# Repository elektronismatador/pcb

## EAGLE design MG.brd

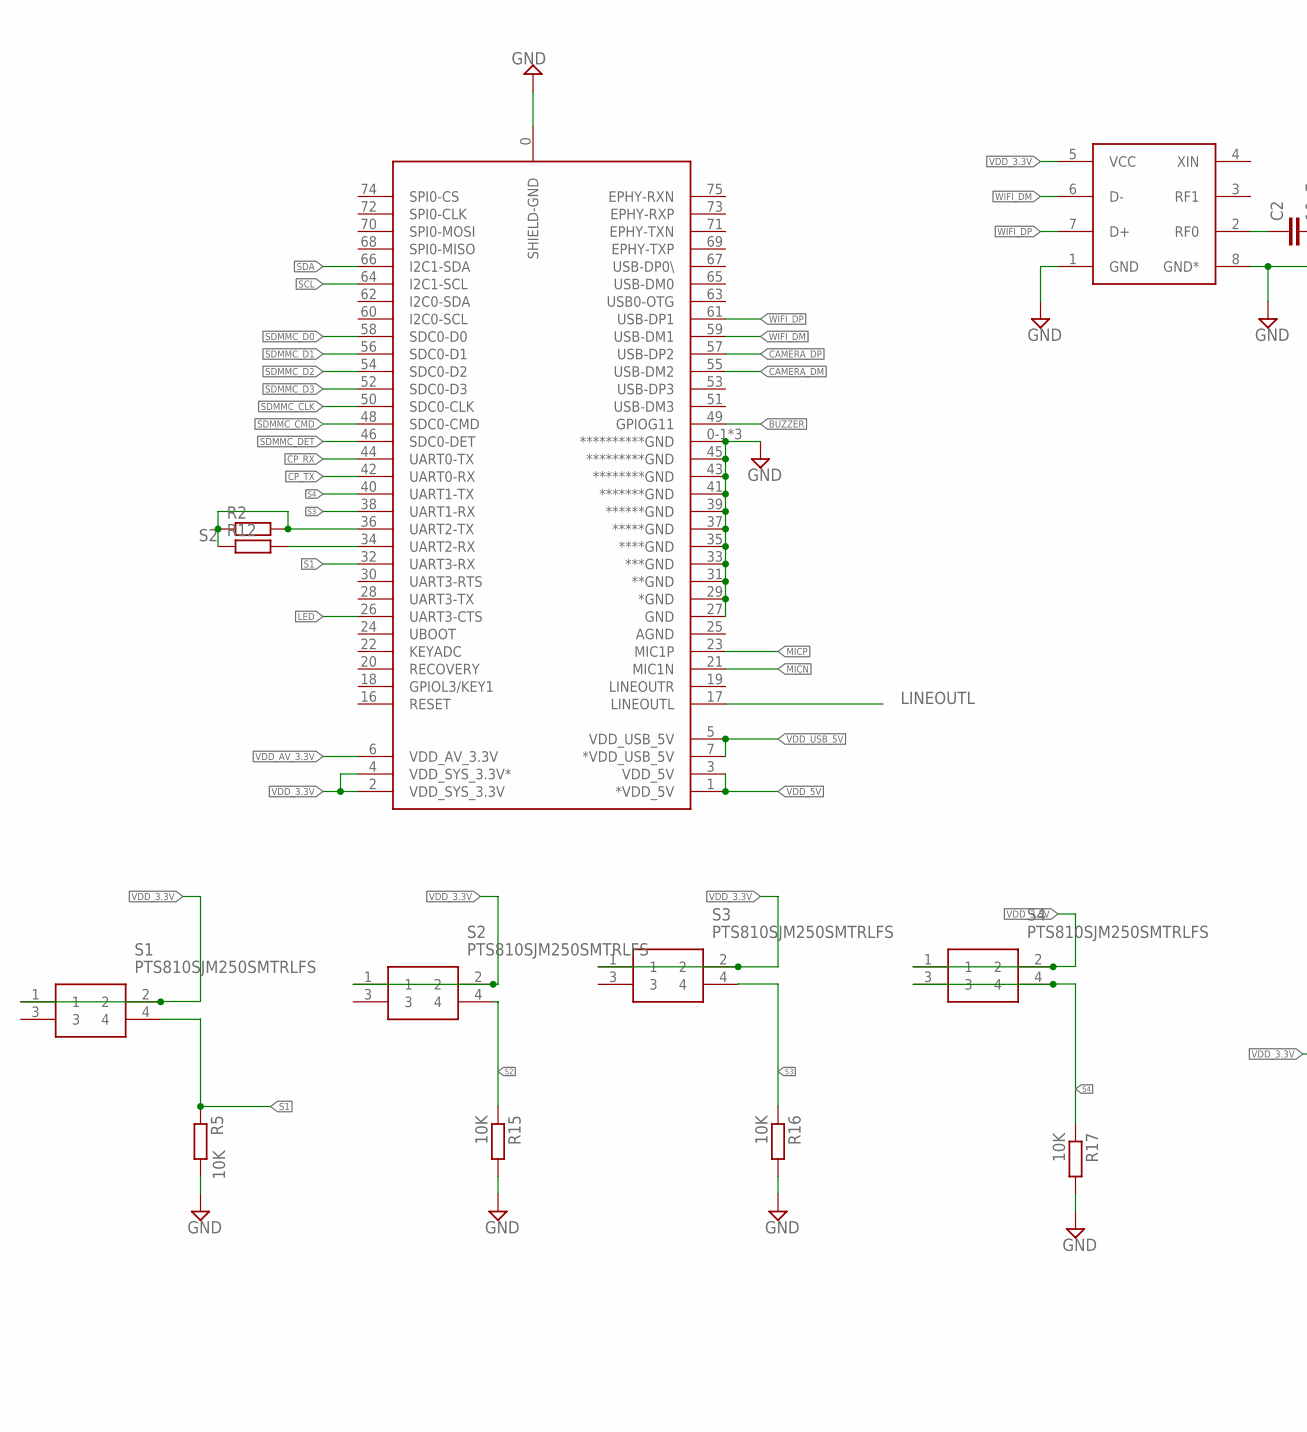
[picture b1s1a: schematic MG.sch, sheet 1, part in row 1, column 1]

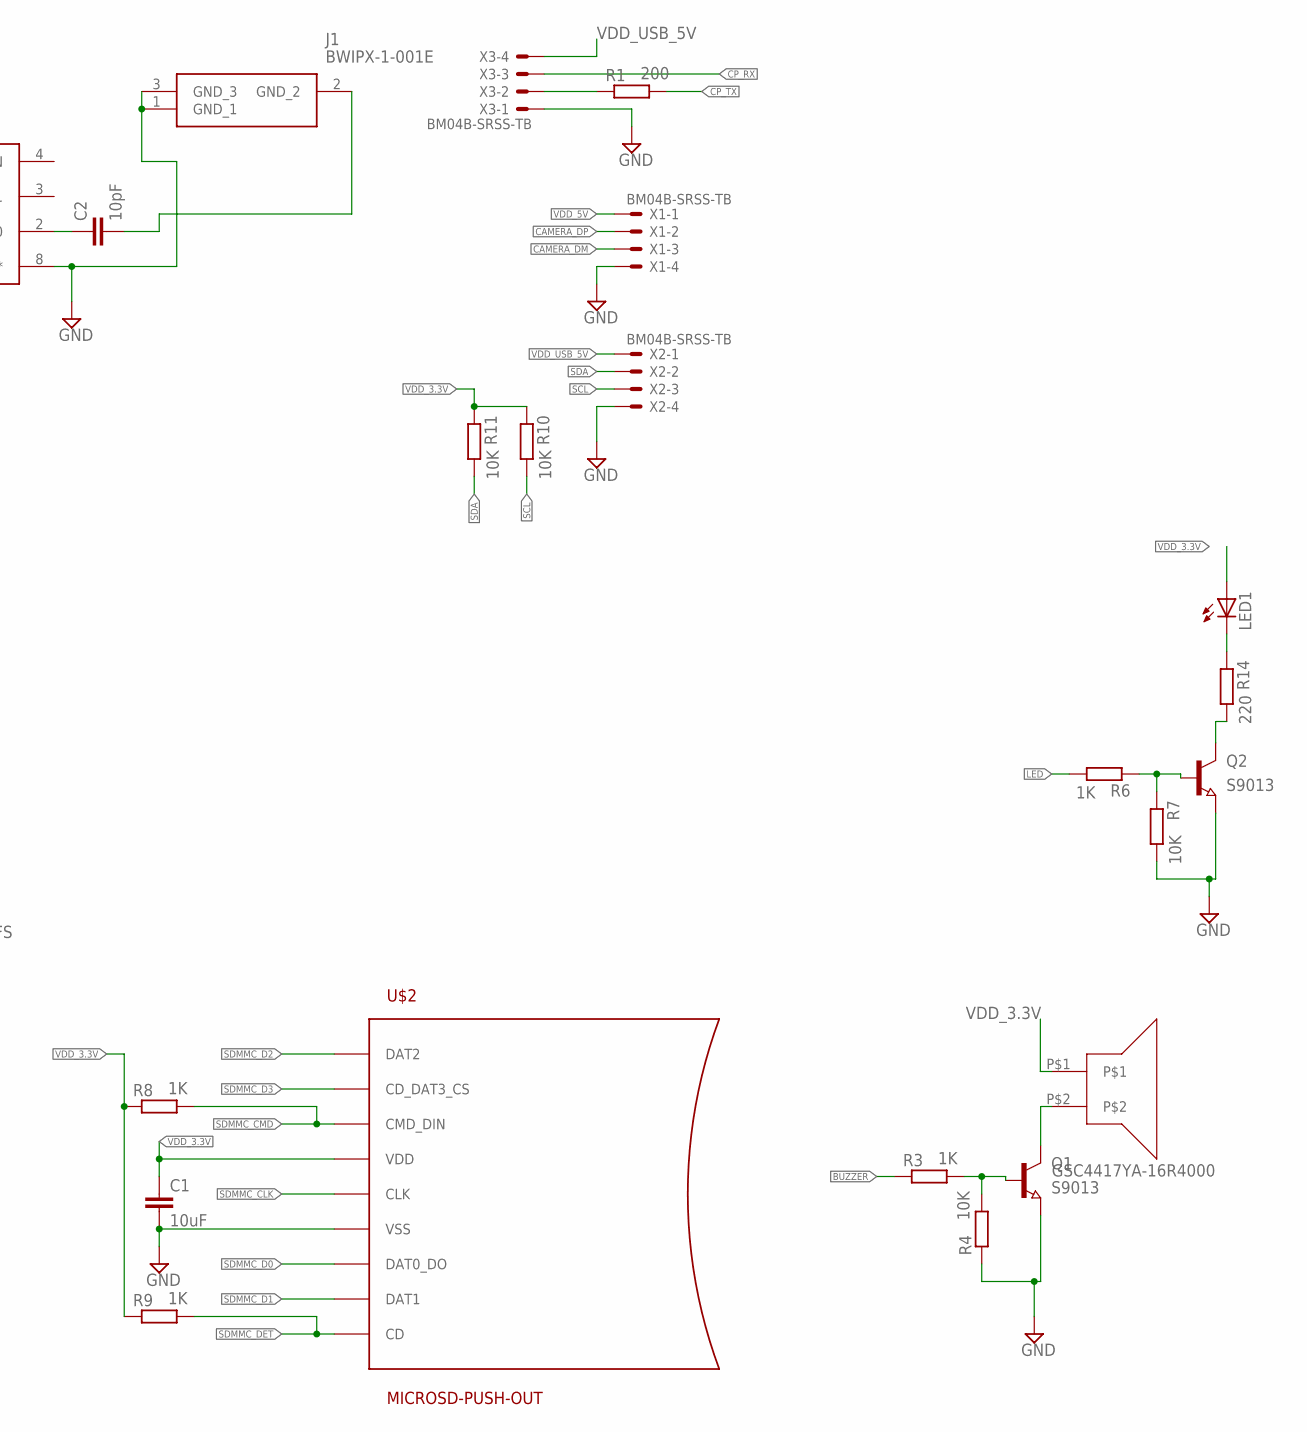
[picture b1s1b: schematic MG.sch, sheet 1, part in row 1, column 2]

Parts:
C1: 10uF; C0603
C2: 10pF; C0603
J1: BWIPX-1-001E; BWIPX1001E
LED1: LEDSML0603; SML0603
Q1, Q2: S9013; SOT23
R1: 200; R0603
R2, R12: R-EU_R0201; R0201
R3, R6, R8, R9: 1K; R0603
R4, R5, R7, R10, R11, R15, R16, R17: 10K; R0603
R14: 220; R0603
S1, S2, S3, S4: PTS810SJM250SMTRLFS; PTS810SJG250SMTRLFS
U$1: QUANTUM-CORE; QUANTUM-QUARK-N
U$2: MICROSD-PUSH-OUT
U$3: WIFI-BT-RTL8723BU; USB-WIFI-BT-RTL8723BU
U$4: GSC4417YA-16R4000
X1, X2, X3: BM04B-SRSS-TB

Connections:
BUZZER: R3.1, U$1.49 (GPIOG11)
CAMERA_DM: U$1.55 (USB-DM2), X1.3
CAMERA_DP: U$1.57 (USB-DP2), X1.2
CP_RX: U$1.44 (UART0-TX), X3.3
CP_TX: R1.2, U$1.42 (UART0-RX)
GND: C1.2, J1.1 (GND_1), J1.3 (GND_3), Q1.2 (E), Q2.2 (E), R4.1, R5.2, R7.2, R15.2, R16.2, R17.2, U$1.0 (SHIELD-GND), U$1.0-1 (**********GND), U$1.0-2 (**********GND), U$1.27 (GND), U$1.29 (*GND), U$1.31 (**GND), U$1.33 (***GND), U$1.35 (****GND), U$1.37 (*****GND), U$1.39 (******GND), U$1.41 (*******GND), U$1.43 (********GND), U$1.45 (*********GND), U$1.47 (**********GND), U$2.6 (VSS), U$2.G1 (VSS), U$2.G2 (VSS), U$2.G3 (VSS), U$2.G4 (VSS), U$3.1 (GND), U$3.8 (GND*), X1.4, X2.4, X3.1; also elsewhere on the board
LED: R6.2, U$1.26 (UART3-CTS)
LINEOUTL: U$1.17 (LINEOUTL); also elsewhere on the board
MICN: U$1.21 (MIC1N)
MICP: U$1.23 (MIC1P)
unnamed: R1.1, X3.2
unnamed: Q1.3 (C), U$4.P$2
unnamed: Q1.1 (B), R3.2, R4.2
unnamed: R12.2, U$1.34 (UART2-RX)
unnamed: C2.2, J1.2 (GND_2)
unnamed: Q2.3 (C), R14.2
unnamed: C2.1, U$3.2 (RF0)
unnamed: LED1.C, R14.1
unnamed: Q2.1 (B), R6.1, R7.1
S1: R5.1, S1.4, U$1.32 (UART3-RX)
S2: R2.1, R2.2, R12.1, R15.1, S2.4, U$1.36 (UART2-TX)
S3: R16.1, S3.4, U$1.38 (UART1-RX)
S4: R17.1, S4.3, S4.4, U$1.40 (UART1-TX)
SCL: R10.2, U$1.64 (I2C1-SCL), X2.3
SDA: R11.2, U$1.66 (I2C1-SDA), X2.2
SDMMC_CLK: U$1.50 (SDC0-CLK), U$2.5 (CLK)
SDMMC_CMD: R8.2, U$1.48 (SDC0-CMD), U$2.3 (CMD_DIN)
SDMMC_D0: U$1.58 (SDC0-D0), U$2.7 (DAT0_DO)
SDMMC_D1: U$1.56 (SDC0-D1), U$2.8 (DAT1)
SDMMC_D2: U$1.54 (SDC0-D2), U$2.1 (DAT2)
SDMMC_D3: U$1.52 (SDC0-D3), U$2.2 (CD_DAT3_CS)
SDMMC_DET: R9.2, U$1.46 (SDC0-DET), U$2.CD
VDD_3.3V: C1.1, LED1.A, R8.1, R9.1, R10.1, R11.1, S1.1, S1.2, S2.1, S2.2, S3.1, S3.2, S4.1, S4.2, U$1.2 (VDD_SYS_3.3V), U$1.4 (VDD_SYS_3.3V*), U$2.4 (VDD), U$3.5 (VCC), U$4.P$1
VDD_5V: U$1.1 (*VDD_5V), U$1.3 (VDD_5V), X1.1; also elsewhere on the board
VDD_AV_3.3V: U$1.6 (VDD_AV_3.3V)
VDD_USB_5V: U$1.5 (VDD_USB_5V), U$1.7 (*VDD_USB_5V), X2.1, X3.4
WIFI_DM: U$1.59 (USB-DM1), U$3.6 (D-)
WIFI_DP: U$1.61 (USB-DP1), U$3.7 (D+)

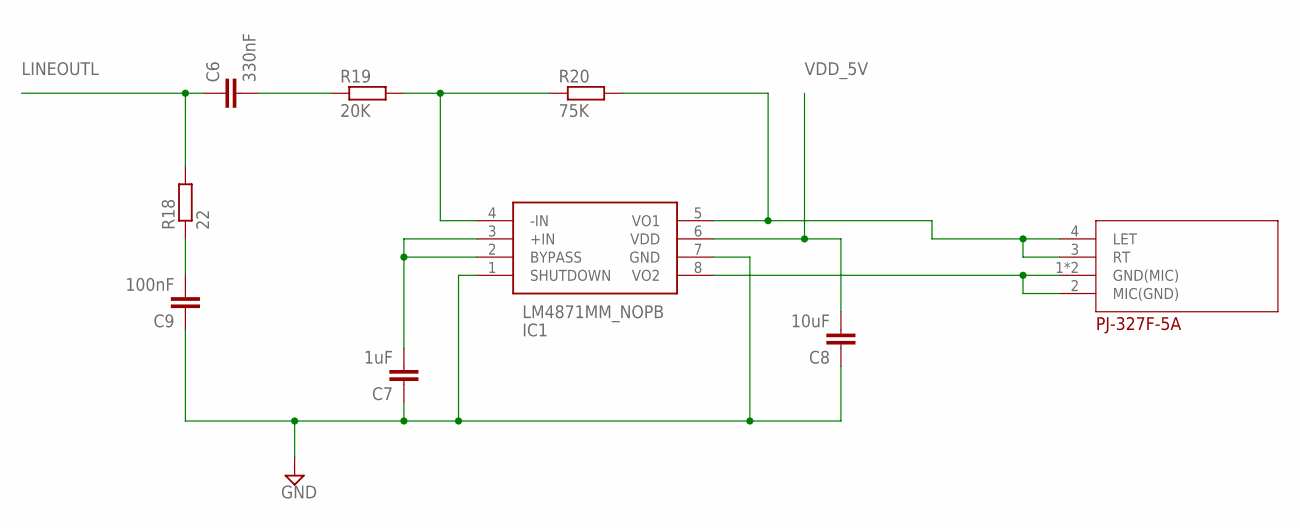
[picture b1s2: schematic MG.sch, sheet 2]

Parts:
C6: 330nF; C0603
C7: 1uF; C0603
C8: 10uF; C0603
C9: 100nF; C0603
IC1: LM4871MM_NOPB; SOP65P490X110-8N
R18: 22; R0603
R19: 20K; R0603
R20: 75K; R0603
U$7: PJ-327F-5A

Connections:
GND: C7.1, C8.1, C9.1, IC1.1 (SHUTDOWN), IC1.7 (GND); also elsewhere on the board
LINEOUTL: C6.1, R18.2; also elsewhere on the board
unnamed: IC1.8 (VO2), U$7.1 (GND(MIC)), U$7.2 (MIC(GND)), U$7.5 (GND(MIC))
unnamed: C7.2, IC1.2 (BYPASS), IC1.3 (+IN)
unnamed: IC1.4 (-IN), R19.2, R20.1
unnamed: C6.2, R19.1
unnamed: C9.2, R18.1
unnamed: IC1.5 (VO1), R20.2, U$7.3 (RT), U$7.4 (LET)
VDD_5V: C8.2, IC1.6 (VDD); also elsewhere on the board

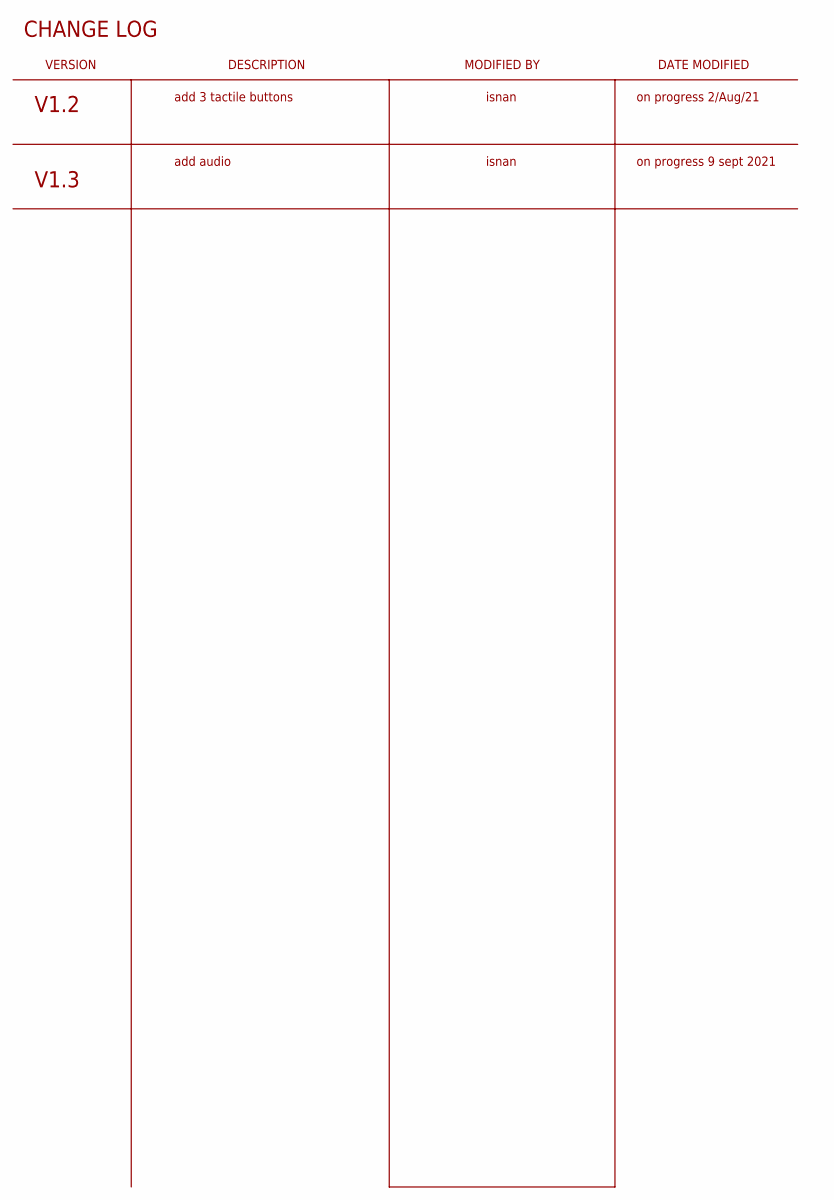
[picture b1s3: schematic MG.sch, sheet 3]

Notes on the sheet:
CHANGE LOG
V1.2
add 3 tactile buttons
VERSION
DESCRIPTION
MODIFIED BY
DATE MODIFIED
isnan
on progress 2/Aug/21
V1.3
add audio
on progress 9 sept 2021

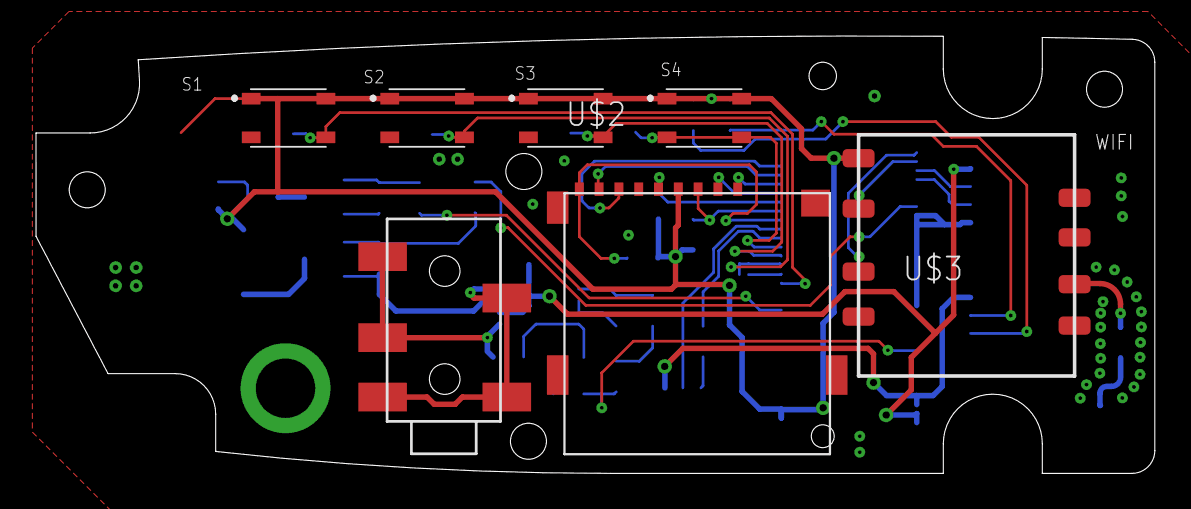
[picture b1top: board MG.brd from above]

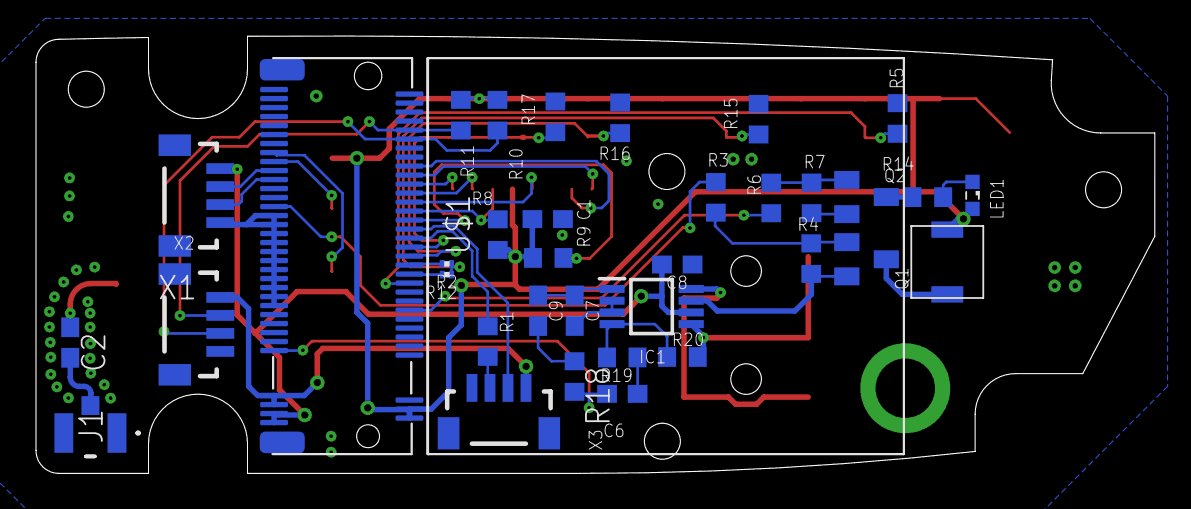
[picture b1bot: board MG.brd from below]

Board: 2 copper layers, 62.2 x 24.3 mm, 42 parts (35 on the bottom side), 41 nets.

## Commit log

2021-10-07 first
2021-10-07 second
